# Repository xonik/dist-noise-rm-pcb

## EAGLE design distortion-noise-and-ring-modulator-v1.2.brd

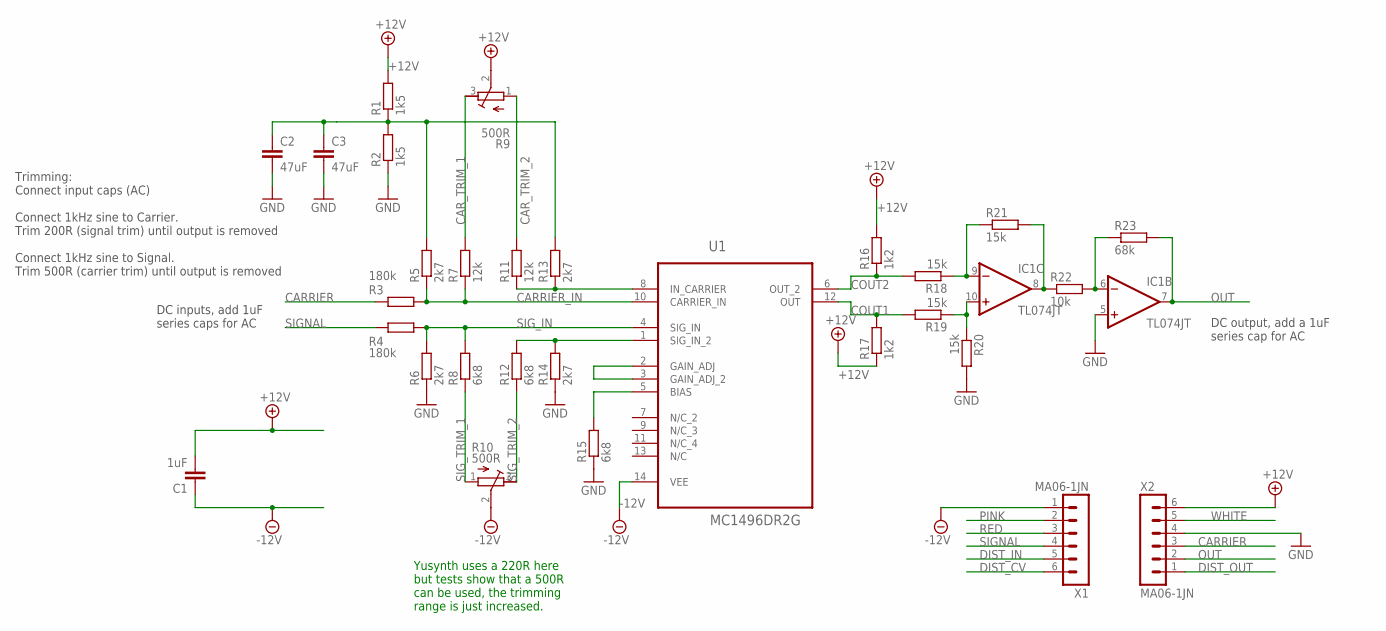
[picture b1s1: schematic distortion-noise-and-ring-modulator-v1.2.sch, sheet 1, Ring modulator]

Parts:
C1: 1uF; C0402-J
C2, C3: 47uF; C1206
IC1: TL074JT; TSSOP14J
R1, R2: 1k5; R0402
R3, R4: 180k; R0402
R5, R6, R13, R14: 2k7; R0603
R7, R11: 12k; R0402
R8, R12, R15: 6k8; R0603
R9, R10: 500R; RTRIM3296X
R16, R17: 1k2; R0603
R18, R19, R20, R21: 15k; R0402
R22: 10k; R0402
R23: 68k; R0603
U1: MC1496DR2G; SOIC127P600X175-14N
X1, X2: MA06-1JN; MA06N-1J

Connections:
+12V: C1.2, R1.2, R9.2 (S), R16.2, R17.1, X2.6; also elsewhere on the board
-12V: C1.1, R10.2 (S), U1.14 (VEE), X1.1; also elsewhere on the board
CARRIER: R3.1, X2.3
CARRIER_IN: R3.2, R5.1, R7.1, U1.10 (CARRIER_IN)
CAR_TRIM_1: R7.2, R9.3 (E)
CAR_TRIM_2: R9.1 (A), R11.2
COUT1: R17.2, R19.2, U1.12 (OUT)
COUT2: R16.1, R18.2, U1.6 (OUT_2)
DIST_CV: X1.6; also elsewhere on the board
DIST_IN: X1.5; also elsewhere on the board
DIST_OUT: X2.1; also elsewhere on the board
GND: C2.2, C3.2, IC1.5 (+IN), R2.1, R6.1, R14.1, R15.1, R20.2, X2.4; also elsewhere on the board
unnamed: R12.2, R14.2, U1.1 (SIG_IN_2)
unnamed: R11.1, R13.1, U1.8 (IN_CARRIER)
unnamed: C2.1, C3.1, R1.1, R2.2, R5.2, R13.2
unnamed: R15.2, U1.5 (BIAS)
unnamed: U1.2 (GAIN_ADJ), U1.3 (GAIN_ADJ_2)
unnamed: IC1.10 (+IN), R19.1, R20.1
unnamed: IC1.9 (-IN), R18.1, R21.1
unnamed: IC1.8 (OUT), R21.2, R22.1
unnamed: IC1.6 (-IN), R22.2, R23.1
OUT: IC1.7 (OUT), R23.2, X2.2
PINK: X1.2; also elsewhere on the board
RED: X1.3; also elsewhere on the board
SIGNAL: R4.1, X1.4
SIG_IN: R4.2, R6.2, R8.2, U1.4 (SIG_IN)
SIG_TRIM_1: R8.1, R10.1 (A)
SIG_TRIM_2: R10.3 (E), R12.1
WHITE: X2.5; also elsewhere on the board

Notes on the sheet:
DC inputs, add 1uF series caps for AC
DC output, add a 1uF series cap for AC
Trimming: Connect input caps (AC) Connect 1kHz sine to Carrier. Trim 200R (signal trim) until output is removed Connect 1kHz sine to Signal. Trim 500R (carrier trim) until output is removed
Yusynth uses a 220R here but tests show that a 500R can be used, the trimming range is just increased.

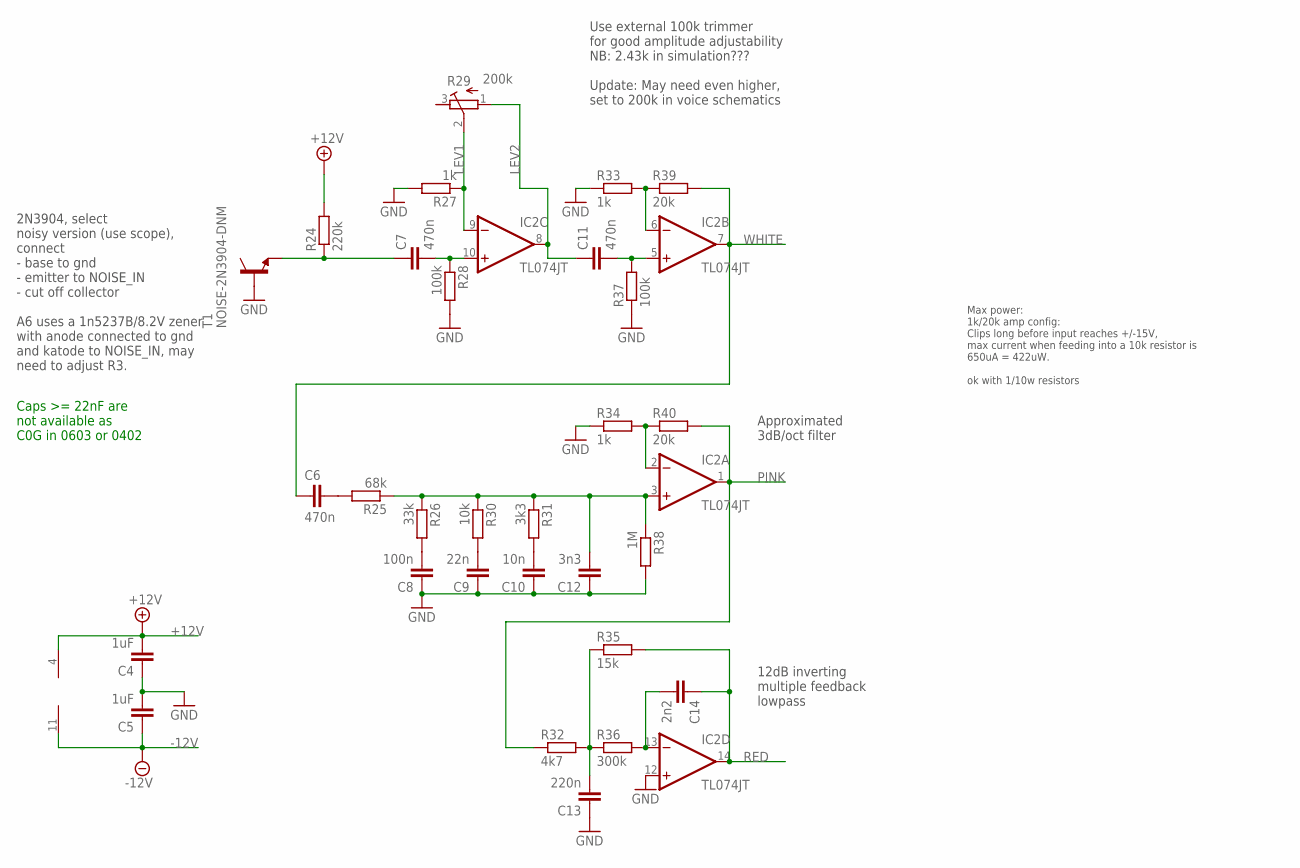
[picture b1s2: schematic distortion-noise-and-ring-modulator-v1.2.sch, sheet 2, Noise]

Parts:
C4, C5: 1uF; C0402-J
C6, C7, C11: 470n; C0603-J
C8: 100n; C0402-J
C9: 22n; C0402-J
C10: 10n; C0402-J
C12: 3n3; C0603-J
C13: 220n; C0402-J
C14: 2n2; C0603-J
IC2: TL074JT; TSSOP14J
R24: 220k; R0603
R25: 68k; R0603
R26: 33k; R0402
R27, R33, R34: 1k; R0402
R28, R37: 100k; R0402
R29: 200k; RTRIM3296W
R30: 10k; R0402
R31: 3k3; R0402
R32: 4k7; R0402
R35: 15k; R0402
R36: 300k; R0603
R38: 1M; R0402
R39, R40: 20k; R0402
T1: NOISE-2N3904-DNM; NOISE-2N3904-J

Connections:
+12V: C4.2, IC2.4 (V+), R24.2; also elsewhere on the board
-12V: C5.1, IC2.11 (V-); also elsewhere on the board
GND: C4.1, C5.2, C8.1, C9.1, C10.1, C12.1, C13.1, IC2.12 (+IN), R27.2, R28.2, R33.1, R34.1, R37.1, R38.2, T1.B; also elsewhere on the board
LEV1: IC2.9 (-IN), R27.1, R29.2 (S)
LEV2: C11.1, IC2.8 (OUT), R29.1 (A)
unnamed: IC2.2 (-IN), R34.2, R40.1
unnamed: IC2.6 (-IN), R33.2, R39.1
unnamed: C8.2, R26.2
unnamed: C9.2, R30.2
unnamed: C10.2, R31.2
unnamed: C7.1, R24.1, T1.E
unnamed: C7.2, IC2.10 (+IN), R28.1
unnamed: C11.2, IC2.5 (+IN), R37.2
unnamed: C12.2, IC2.3 (+IN), R25.1, R26.1, R30.1, R31.1, R38.1
unnamed: C6.2, R25.2
unnamed: C13.2, R32.2, R35.1, R36.1
unnamed: C14.2, IC2.13 (-IN), R36.2
PINK: IC2.1 (OUT), R32.1, R40.2; also elsewhere on the board
RED: C14.1, IC2.14 (OUT), R35.2; also elsewhere on the board
WHITE: C6.1, IC2.7 (OUT), R39.2; also elsewhere on the board

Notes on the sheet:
Use external 100k trimmer for good amplitude adjustability NB: 2.43k in simulation??? Update: May need even higher, set to 200k in voice schematics
Approximated 3dB/oct filter
12dB inverting multiple feedback lowpass
2N3904, select noisy version (use scope), connect - base to gnd - emitter to NOISE_IN - cut off collector A6 uses a 1n5237B/8.2V zener with anode connected to gnd and katode to NOISE_IN, may need to adjust R3.
Max power: 1k/20k amp config: Clips long before input reaches +/-15V, max current when feeding into a 10k resistor is 650uA = 422uW. ok with 1/10w resistors
Caps >= 22nF are not available as C0G in 0603 or 0402

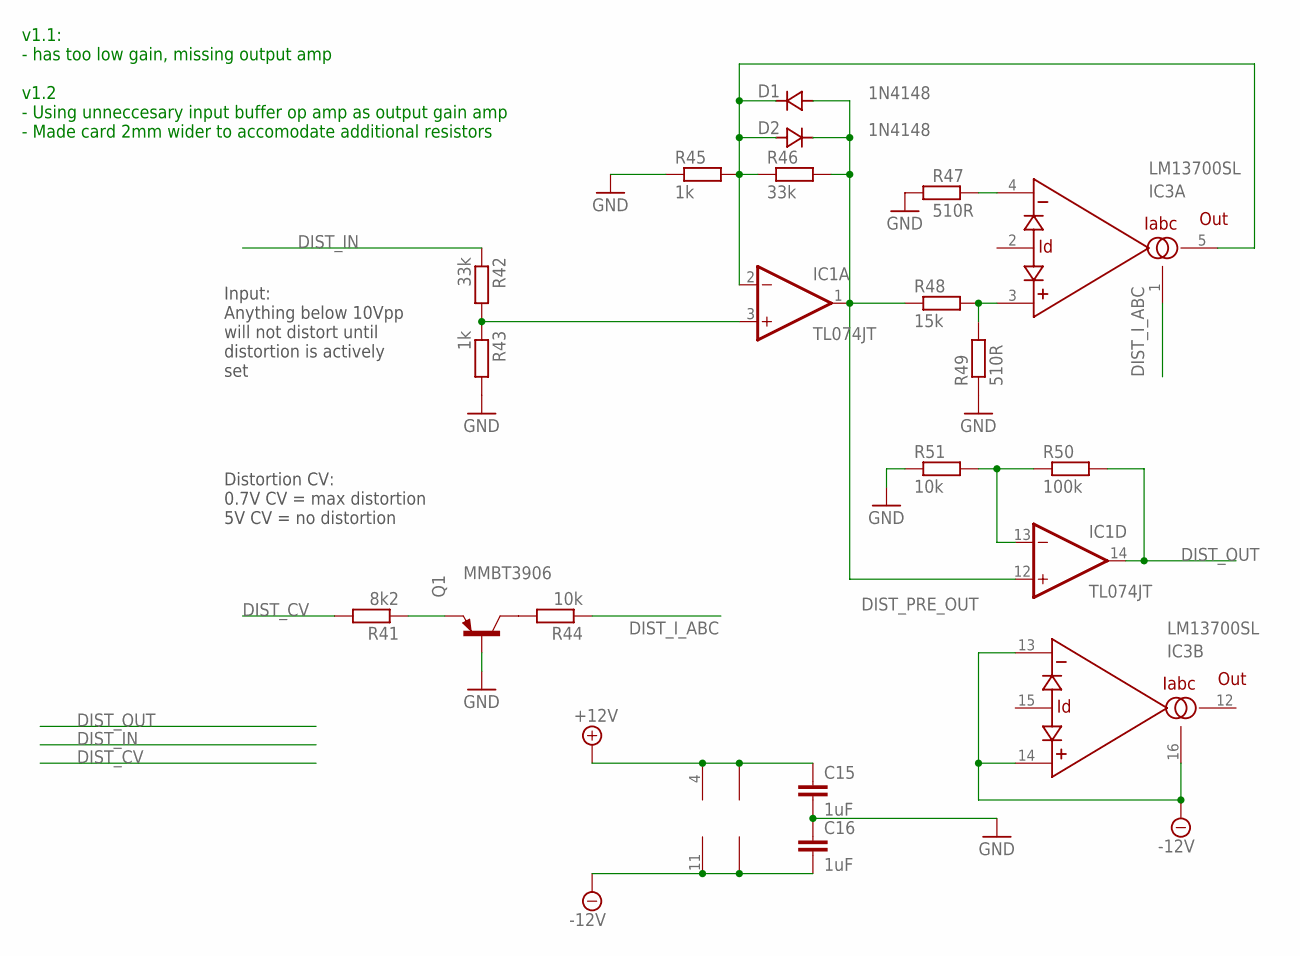
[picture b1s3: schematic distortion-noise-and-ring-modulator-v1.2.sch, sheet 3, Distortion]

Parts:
C15, C16: 1uF; C0402-J
D1, D2: 1N4148; SOD323J
IC1: TL074JT; TSSOP14J
IC3: LM13700SL; SO16-NARROW-J
Q1: MMBT3906; SOT23-BEC
R41: 8k2; R0603
R42, R46: 33k; R0402
R43, R45: 1k; R0402
R44, R51: 10k; R0402
R47, R49: 510R; R0402
R48: 15k; R0402
R50: 100k; R0402

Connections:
+12V: C15.1, IC1.4 (V+), IC3.11 (V+); also elsewhere on the board
-12V: C16.2, IC1.11 (V-), IC3.6 (V-), IC3.13 (-IN), IC3.14 (+IN), IC3.16 (IABC); also elsewhere on the board
DIST_CV: R41.2; also elsewhere on the board
DIST_IN: R42.1; also elsewhere on the board
DIST_I_ABC: IC3.1 (IABC), R44.1
DIST_OUT: IC1.14 (OUT), R50.2; also elsewhere on the board
DIST_PRE_OUT: D1.2 (A), D2.1 (C), IC1.1 (OUT), IC1.12 (+IN), R46.2, R48.1
GND: C15.2, C16.1, Q1.B, R43.2, R45.1, R47.1, R49.1, R51.1; also elsewhere on the board
unnamed: IC1.3 (+IN), R42.2, R43.1
unnamed: IC1.13 (-IN), R50.1, R51.2
unnamed: D1.1 (C), D2.2 (A), IC1.2 (-IN), IC3.5 (OUT), R45.2, R46.1
unnamed: IC3.4 (-IN), R47.2
unnamed: IC3.3 (+IN), R48.2, R49.2
unnamed: Q1.E, R41.1
unnamed: Q1.C, R44.2

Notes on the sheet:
Distortion CV: 0.7V CV = max distortion 5V CV = no distortion
Input: Anything below 10Vpp will not distort until distortion is actively set
v1.1: - has too low gain, missing output amp v1.2 - Using unneccesary input buffer op amp as output gain amp - Made card 2mm wider to accomodate additional resistors

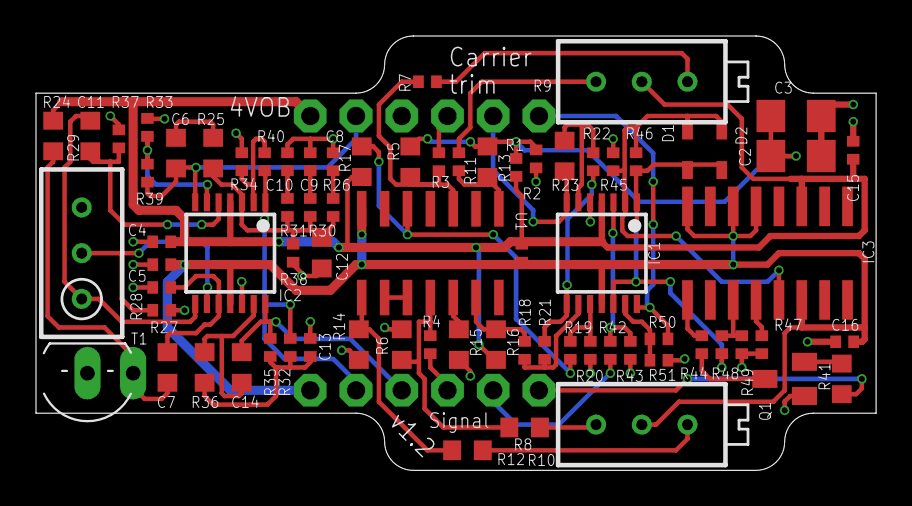
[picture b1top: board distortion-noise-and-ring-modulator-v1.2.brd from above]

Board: 2 copper layers, 46.7 x 24.1 mm, 77 parts (0 on the bottom side), 52 nets.

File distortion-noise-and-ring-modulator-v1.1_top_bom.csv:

Comment,Designator,Footprint,LCSC Part #
1M,R38,R0402,
1N4148,D1 D2,SOD323J,
1k,R27 R33 R34 R43 R45,R0402,
1k2,R16 R17,R0603,
1k5,R1 R2,R0402,
1uF,C1 C4 C5 C15 C16,C0402-J,
2k7,R5 R6 R13 R14,R0603,
2n2,C14,C0603-J,
3k3,R31,R0402,
3n3,C12,C0603-J,
4k7,R32,R0402,
6k8,R8 R12 R15,R0603,
8k2,R41,R0603,
10k,R22 R30 R44,R0402,
10n,C10,C0402-J,
12k,R7 R11,R0402,
15k,R18 R19 R20 R21 R35 R48,R0402,
20k,R39 R40,R0402,
22n,C9,C0402-J,
33k,R26 R42 R46,R0402,
47uF,C2 C3,C1206,
68k,R23 R25,R0603,
100k,R28 R37,R0402,
100n,C8,C0402-J,
180k,R3 R4,R0402,
200k,R29,RTRIM3296W,
220k,R24,R0603,
220n,C13,C0402-J,
300k,R36,R0603,
470n,C6 C7 C11,C0603-J,
500R,R9 R10,RTRIM3296X,
510R,R47 R49,R0402,
LM13700SL,IC3,SO16-NARROW-J,
MA06-1JN,X1 X2,MA06N-1J,
MC1496DR2G,U1,SOIC127P600X175-14N,
MMBT3906,Q1,SOT23-BEC,
NOISE-2N3904,T1,NOISE-2N3904-J,
TL074JT,IC1 IC2,TSSOP14J,

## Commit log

2025-01-01 Moved multi-fx to separate repo
2025-05-18 Routed v1.2
2025-05-18 Adjust silk screen
2025-05-18 Tested and ready for production
2025-08-10 Tested bom and gerber, v1.2
